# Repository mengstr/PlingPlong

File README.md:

## PingPlong

This is a small (10x20cm 4x8") portable battery-operated synth with a two octave touch keyboard and four voice polyphonic digital sound. A video of the board in action is available at http://youtu.be/FlVGMttL9SU

Two microcontrollers are used on the board - a Microchip PIC18F44K22 for the user interface and a Atmel ATMEGA328 for the sound generation.

The PIC18 is using the internal CMTU module for capacitively sensing the 24 touch keys. It is also in charge of scanning the 15 tactile buttons, refreshing the 15 status LEDs and the 7-segment displays, and polling the Rotary Encoder.

Whenever a padis touched or the rotary encoder is turned a standard Note On/Off or Control Change MIDI message is sent to the ATMEGA328 for playing.

Currently the MEGA328 is running a straight copy of the [Midi Vampire-I](http://wiki.openmusiclabs.com/wiki/MidiVamp1) firmware. The MEGA328 is also connected to a SD-card connector for future use - I want to do firmware updates via the SD card.

The sound-generating part is contained in a 5x5cm "selfcontained" area to the right on the pcb having pads and via holes for power, midi and SD-card signals. This makes it easy to replace just the synth with something else than the MidiVamp. Just design a new 5x5 cm pcb and solder it to the pads on the main board and it's done.

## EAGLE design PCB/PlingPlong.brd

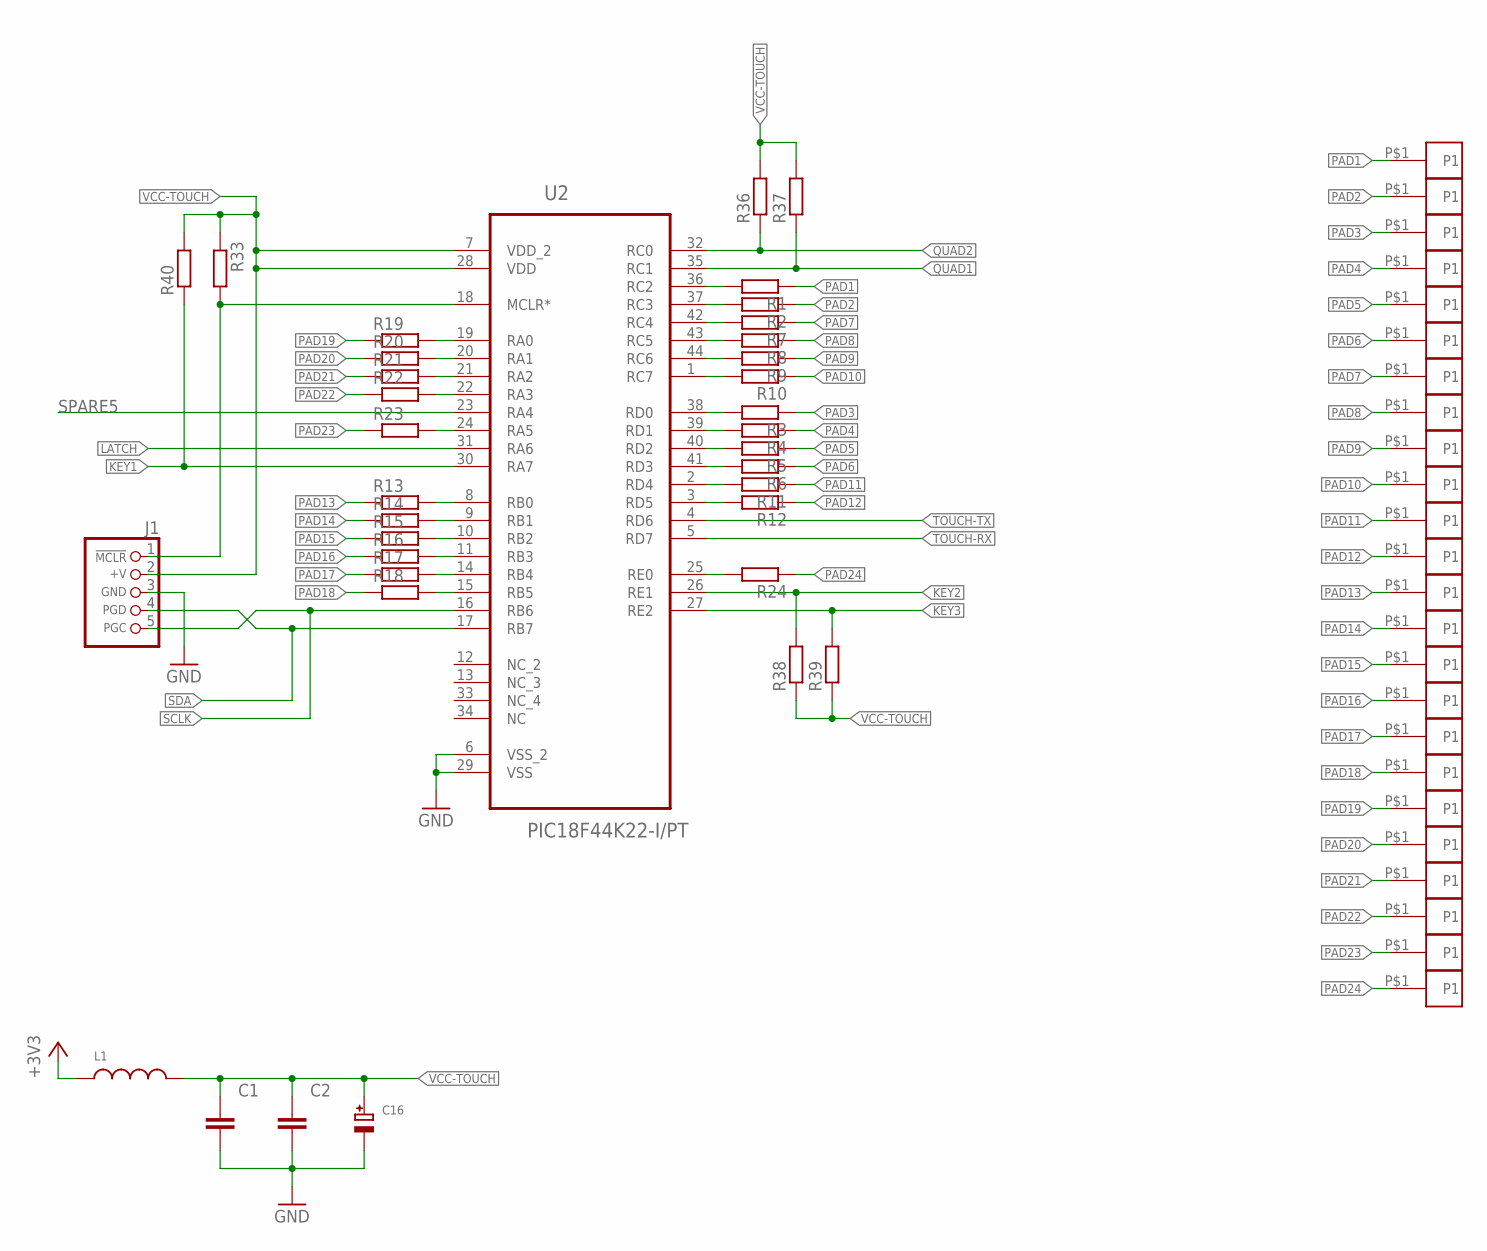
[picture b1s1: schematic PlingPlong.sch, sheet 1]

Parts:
C1, C2: CAPACITOR_NPOL-0805; C805
C16: CAP_TANTALUMD/7343_WAVE; EIA7343-31/D-W
J1: CON_HEADER_PRG_PIC_ICSPB; HEADER_PRG_1X05_ICSP_B
L1: INDUCTOR0805; 0805
P1, P2, P3, P4, P5, P6, P7, P8, P9, P10, P11, P12, P13, P14, P15, P16, P17, P18, P19, P20, P21, P22, P23, P24: PAD-NOSTOP; PAD1X1NOSTOP
R1, R2, R3, R4, R5, R6, R7, R8, R9, R10, R11, R12, R13, R14, R15, R16, R17, R18, R19, R20, R21, R22, R23, R24, R33, R36, R37, R38, R39, R40: R-EU_R0805W; R0805W
U2: PIC18F44K22-I/PT; QFP80P1200X1200X120-44N

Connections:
+3V3: L1.1; also elsewhere on the board
GND: C1.2, C2.2, C16.-, J1.3 (GND), U2.6 (VSS_2), U2.29 (VSS); also elsewhere on the board
KEY1: R40.1, U2.30 (RA7); also elsewhere on the board
KEY2: R38.2, U2.26 (RE1); also elsewhere on the board
KEY3: R39.2, U2.27 (RE2); also elsewhere on the board
LATCH: U2.31 (RA6); also elsewhere on the board
unnamed: R13.2, U2.8 (RB0)
unnamed: R14.2, U2.9 (RB1)
unnamed: R15.2, U2.10 (RB2)
unnamed: R16.2, U2.11 (RB3)
unnamed: R17.2, U2.14 (RB4)
unnamed: R18.2, U2.15 (RB5)
unnamed: R23.2, U2.24 (RA5)
unnamed: R19.2, U2.19 (RA0)
unnamed: R20.2, U2.20 (RA1)
unnamed: R21.2, U2.21 (RA2)
unnamed: R22.2, U2.22 (RA3)
unnamed: R1.2, U2.36 (RC2)
unnamed: R2.2, U2.37 (RC3)
unnamed: R7.2, U2.42 (RC4)
unnamed: R8.2, U2.43 (RC5)
unnamed: R9.2, U2.44 (RC6)
unnamed: R10.2, U2.1 (RC7)
unnamed: R24.2, U2.25 (RE0)
unnamed: J1.1 (/MCLR), R33.2, U2.18 (MCLR*)
unnamed: R12.2, U2.3 (RD5)
unnamed: R11.2, U2.2 (RD4)
unnamed: R6.2, U2.41 (RD3)
unnamed: R5.2, U2.40 (RD2)
unnamed: R4.2, U2.39 (RD1)
unnamed: R3.2, U2.38 (RD0)
PAD1: P1.P$1, R1.1
PAD2: P2.P$1, R2.1
PAD3: P3.P$1, R3.1
PAD4: P4.P$1, R4.1
PAD5: P5.P$1, R5.1
PAD6: P6.P$1, R6.1
PAD7: P7.P$1, R7.1
PAD8: P8.P$1, R8.1
PAD9: P9.P$1, R9.1
PAD10: P10.P$1, R10.1
PAD11: P11.P$1, R11.1
PAD12: P12.P$1, R12.1
PAD13: P13.P$1, R13.1
PAD14: P14.P$1, R14.1
PAD15: P15.P$1, R15.1
PAD16: P16.P$1, R16.1
PAD17: P17.P$1, R17.1
PAD18: P18.P$1, R18.1
PAD19: P19.P$1, R19.1
PAD20: P20.P$1, R20.1
PAD21: P21.P$1, R21.1
PAD22: P22.P$1, R22.1
PAD23: P23.P$1, R23.1
PAD24: P24.P$1, R24.1
QUAD1: R37.1, U2.35 (RC1); also elsewhere on the board
QUAD2: R36.1, U2.32 (RC0); also elsewhere on the board
SCLK: J1.5 (PGC), U2.16 (RB6); also elsewhere on the board
SDA: J1.4 (PGD), U2.17 (RB7); also elsewhere on the board
SPARE5: U2.23 (RA4)
TOUCH-RX: U2.5 (RD7); also elsewhere on the board
TOUCH-TX: U2.4 (RD6); also elsewhere on the board
VCC-TOUCH: C1.1, C2.1, C16.+, J1.2 (+V), L1.2, R33.1, R36.2, R37.2, R38.1, R39.1, R40.2, U2.7 (VDD_2), U2.28 (VDD)

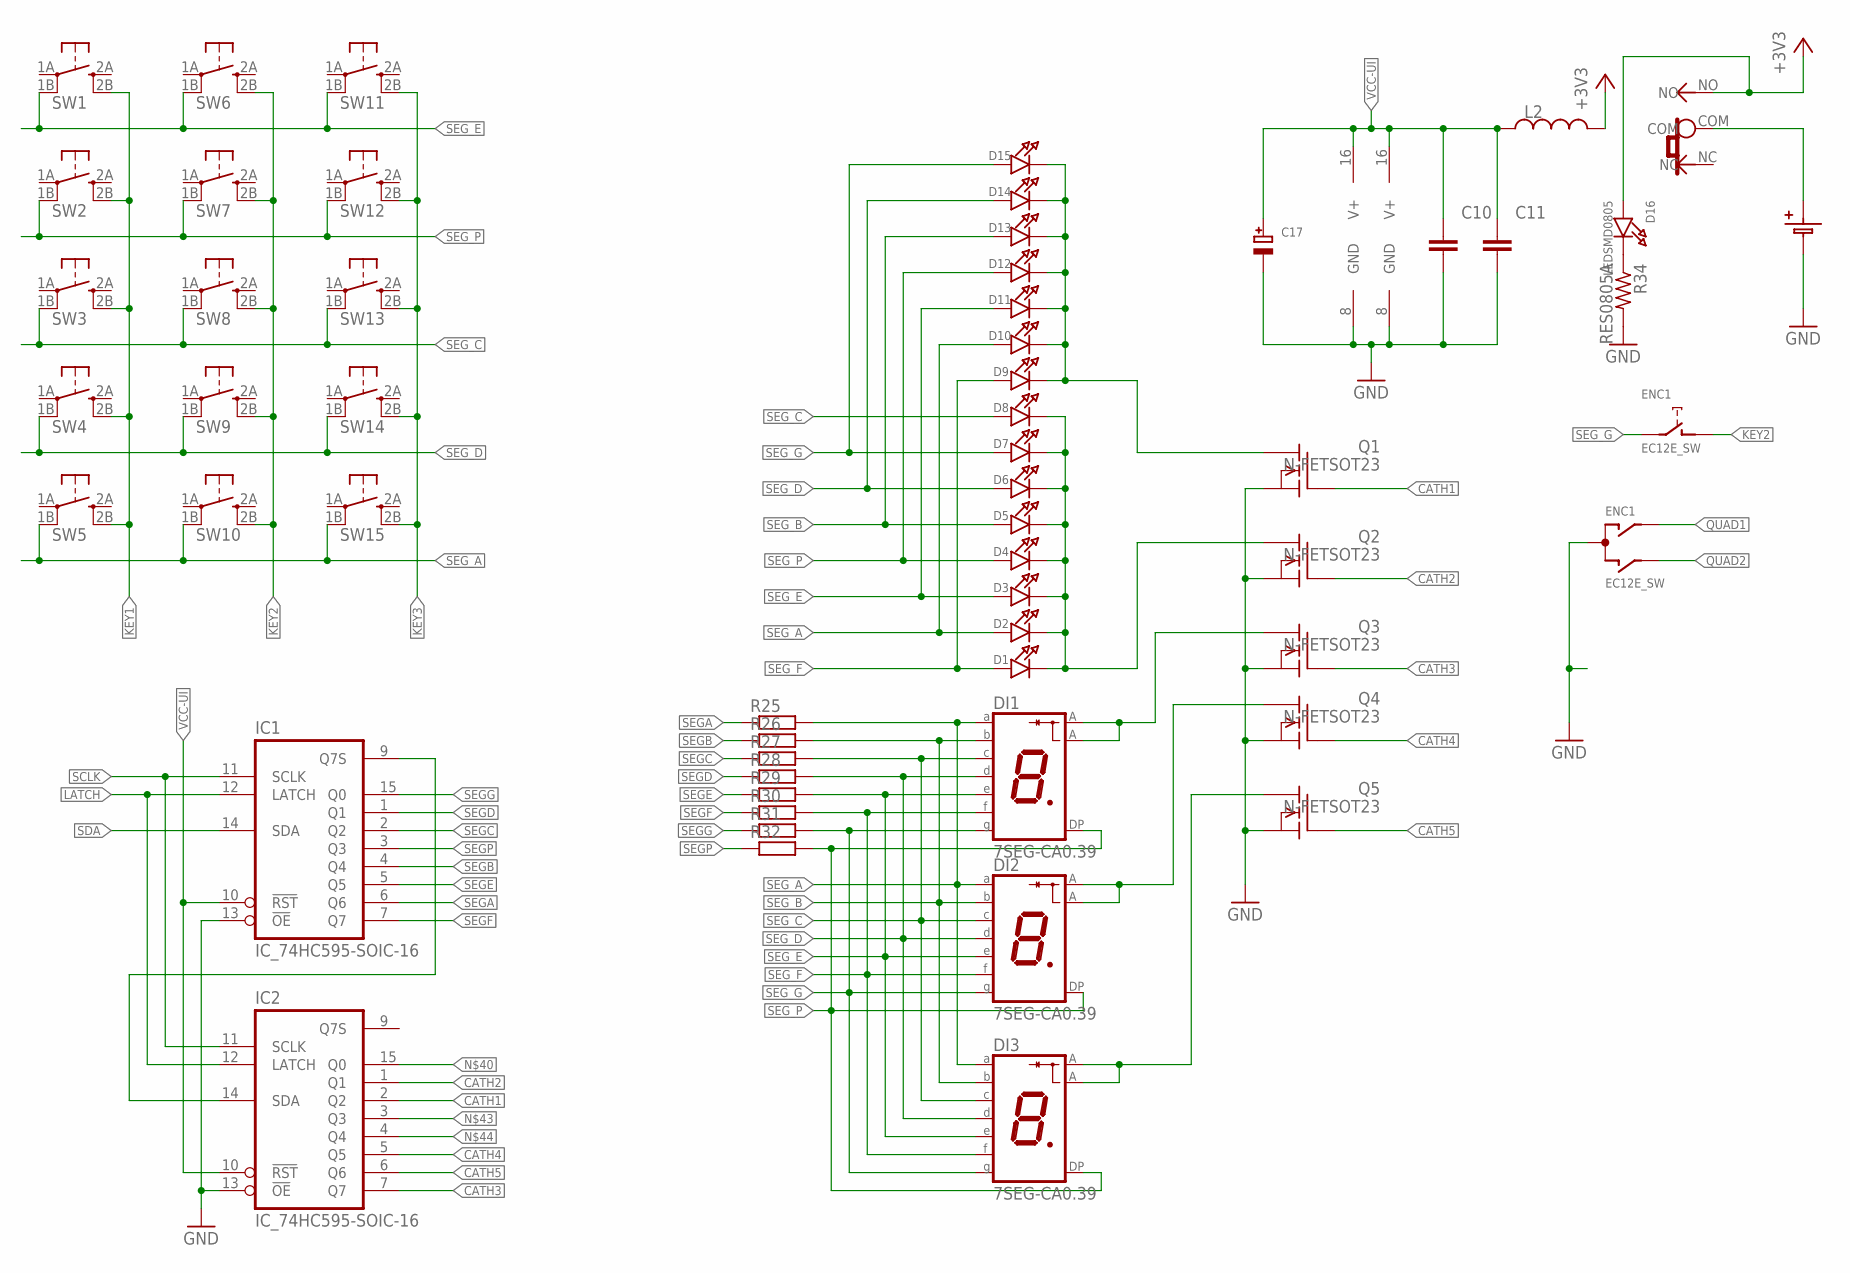
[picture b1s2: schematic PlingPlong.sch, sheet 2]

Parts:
BA1: BATTERY1-123PIN; BATTERY-CR123A-PINS
C10, C11: CAPACITOR_NPOL-0805; C805
C17: CAP_TANTALUMD/7343_WAVE; EIA7343-31/D-W
D1, D2, D3, D4, D5, D6, D7, D8, D9, D10, D11, D12, D13, D14, D15: LED3MM
D16: LEDSMD0805; CHIPLED_0805
DI1, DI2, DI3: 7SEG-CA0.39; LG3911
ENC1: EC12E_SW; ALPS_EC12E_SW
IC1, IC2: IC_74HC595-SOIC-16; SOIC-16
L2: INDUCTOR0805; 0805
Q1, Q2, Q3, Q4, Q5: N-FETSOT23; SOT23
R25, R26, R27, R28, R29, R30, R31, R32: R-EU_R0805W; R0805W
R34: RES0805A; R0805A
SW1, SW2, SW3, SW4, SW5, SW6, SW7, SW8, SW9, SW10, SW11, SW12, SW13, SW14, SW15: TACTILETACT-6X6-PTH; TACTILE-PTH
SW16: SLIDESWITCH-PCM12; PCM12

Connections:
+3V3: D16.A, L2.2, SW16.NO; also elsewhere on the board
CATH1: IC2.2 (Q2), Q1.1 (G)
CATH2: IC2.1 (Q1), Q2.1 (G)
CATH3: IC2.7 (Q7), Q3.1 (G)
CATH4: IC2.5 (Q5), Q4.1 (G)
CATH5: IC2.6 (Q6), Q5.1 (G)
CATH_1: D9.C, D10.C, D11.C, D12.C, D13.C, D14.C, D15.C, Q1.3 (D)
CATH_2: D1.C, D2.C, D3.C, D4.C, D5.C, D6.C, D7.C, D8.C, Q2.3 (D)
CATH_3: DI1.P$3 (A), DI1.P$8 (A), Q3.3 (D)
CATH_4: DI2.P$3 (A), DI2.P$8 (A), Q4.3 (D)
CATH_5: DI3.P$3 (A), DI3.P$8 (A), Q5.3 (D)
GND: BA1.NEG, C10.2, C11.2, C17.-, ENC1.C, IC1.8 (GND), IC1.13 (!OE), IC2.8 (GND), IC2.13 (!OE), Q1.2 (S), Q2.2 (S), Q3.2 (S), Q4.2 (S), Q5.2 (S), R34.2; also elsewhere on the board
KEY1: SW1.2B, SW2.2B, SW3.2B, SW4.2B, SW5.2B; also elsewhere on the board
KEY2: ENC1.D (1), SW6.2B, SW7.2B, SW8.2B, SW9.2B, SW10.2B; also elsewhere on the board
KEY3: SW11.2B, SW12.2B, SW13.2B, SW14.2B, SW15.2B; also elsewhere on the board
LATCH: IC1.12 (LATCH), IC2.12 (LATCH); also elsewhere on the board
unnamed: IC1.9 (Q7S), IC2.14 (SDA)
unnamed: BA1.POS (POS1), SW16.COM
unnamed: D16.C, R34.1
QUAD1: ENC1.A; also elsewhere on the board
QUAD2: ENC1.B; also elsewhere on the board
SCLK: IC1.11 (SCLK), IC2.11 (SCLK); also elsewhere on the board
SDA: IC1.14 (SDA); also elsewhere on the board
SEGA: IC1.6 (Q6), R25.1
SEGB: IC1.4 (Q4), R26.1
SEGC: IC1.2 (Q2), R27.1
SEGD: IC1.1 (Q1), R28.1
SEGE: IC1.5 (Q5), R29.1
SEGF: IC1.7 (Q7), R30.1
SEGG: IC1.15 (Q0), R31.1
SEGP: IC1.3 (Q3), R32.1
SEG_A: D2.A, D10.A, DI1.P$10 (A), DI2.P$10 (A), DI3.P$10 (A), R25.2, SW5.1B, SW10.1B, SW15.1B
SEG_B: D5.A, D13.A, DI1.P$9 (B), DI2.P$9 (B), DI3.P$9 (B), R26.2
SEG_C: D8.A, DI1.P$7 (C), DI2.P$7 (C), DI3.P$7 (C), R27.2, SW3.1B, SW8.1B, SW13.1B
SEG_D: D6.A, D14.A, DI1.P$5 (D), DI2.P$5 (D), DI3.P$5 (D), R28.2, SW4.1B, SW9.1B, SW14.1B
SEG_E: D3.A, D11.A, DI1.P$2 (E), DI2.P$2 (E), DI3.P$2 (E), R29.2, SW1.1B, SW6.1B, SW11.1B
SEG_F: D1.A, D9.A, DI1.P$1 (F), DI2.P$1 (F), DI3.P$1 (F), R30.2
SEG_G: D7.A, D15.A, DI1.P$6 (G), DI2.P$6 (G), DI3.P$6 (G), ENC1.E (2), R31.2
SEG_P: D4.A, D12.A, DI1.P$4 (DP), DI2.P$4 (DP), DI3.P$4 (DP), R32.2, SW2.1B, SW7.1B, SW12.1B
VCC-UI: C10.1, C11.1, C17.+, IC1.10 (!RST), IC1.16 (V+), IC2.10 (!RST), IC2.16 (V+), L2.1

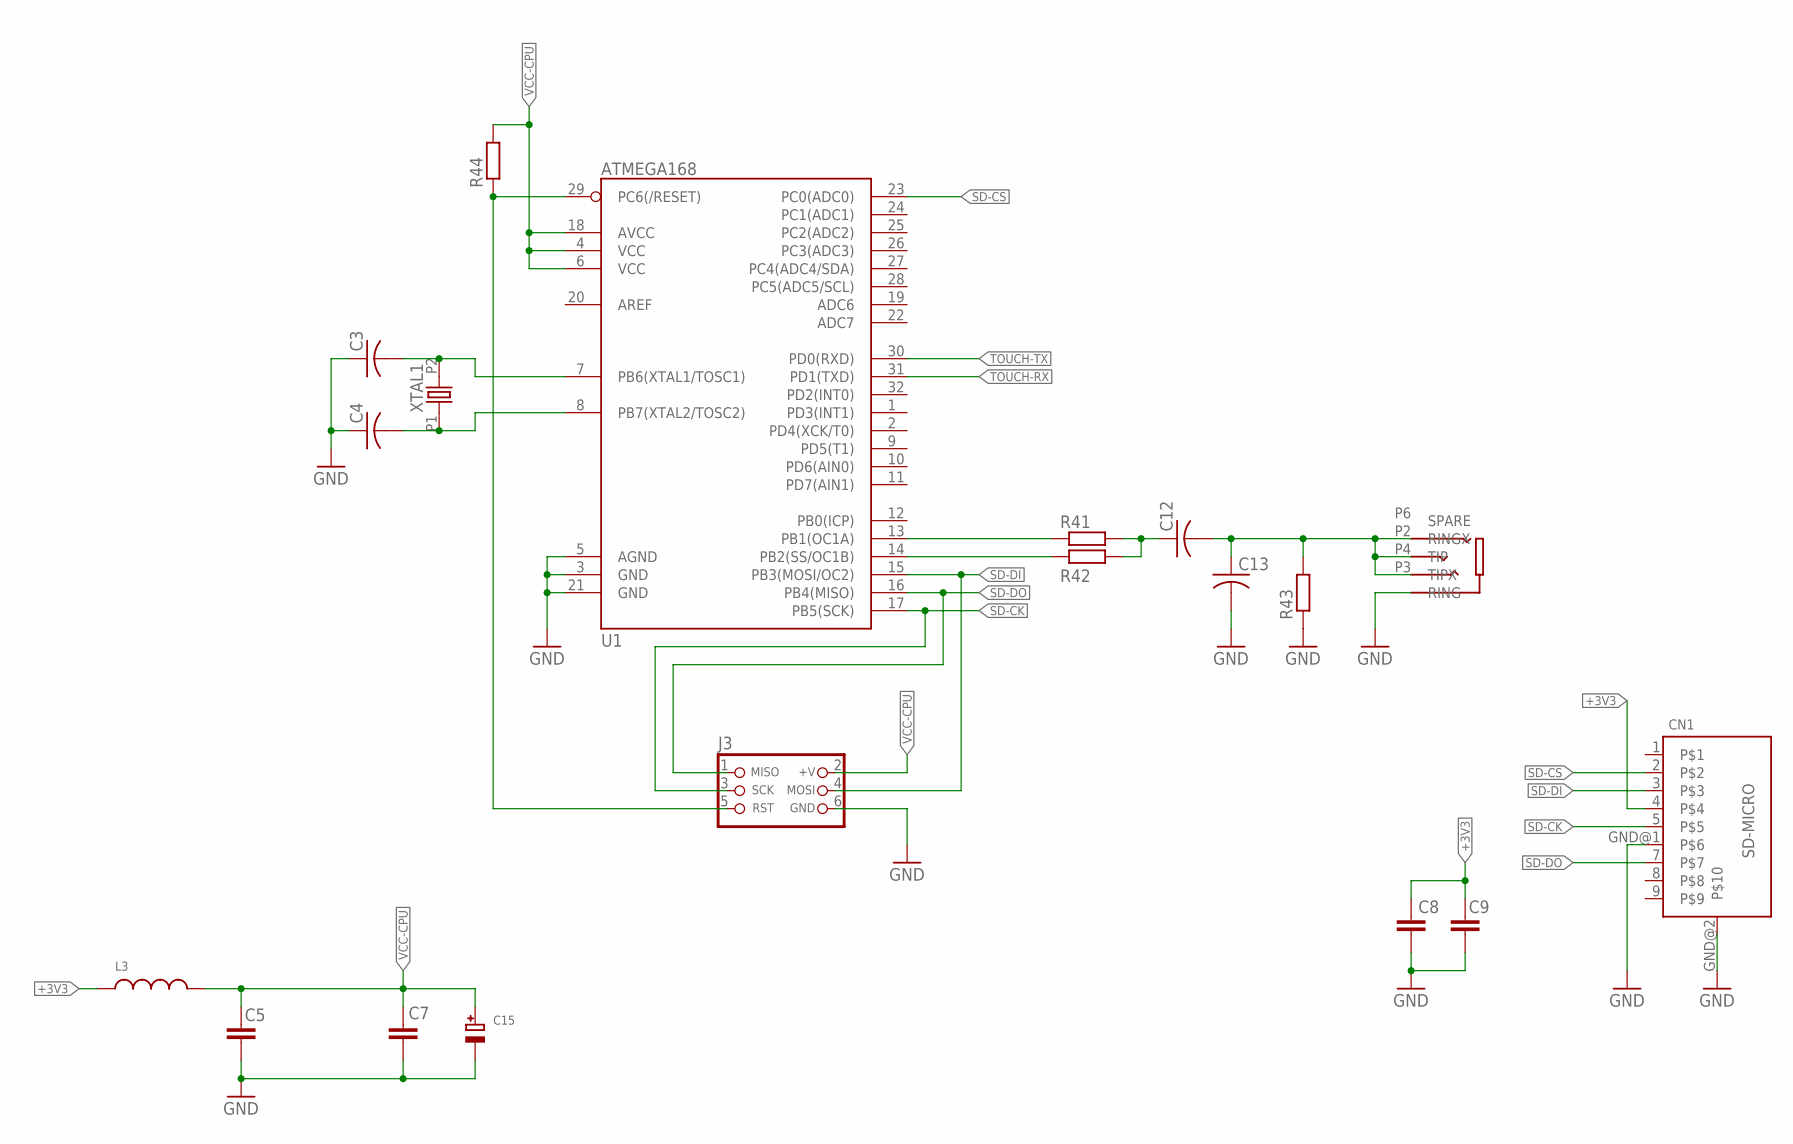
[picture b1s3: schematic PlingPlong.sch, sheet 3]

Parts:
C3, C4, C13: C-USC0805; C0805
C5, C7, C8, C9: CAPACITOR_NPOL-0805; C805
C12: C-USC1206; C1206
C15: CAP_TANTALUMD/7343_WAVE; EIA7343-31/D-W
CN1: SD-MICRO; MICROSD-TFP09
J3: CON_HEADER_PRG_AVR_ICSP; HEADER_PRG_2X03
L3: INDUCTOR0805; 0805
R41, R42, R43, R44: R-EU_R0805W; R0805W
U1: ATMEGA168; TQFP32-08
U$2: JACK4-PJ320; PJ-320E
XTAL1: OSC-XTAL-HC-49U-PTH; HC-49U-PTH

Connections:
+3V3: C8.1, C9.1, CN1.4, L3.1; also elsewhere on the board
CPU-RESET: J3.5 (RST), R44.1, U1.29 (PC6(/RESET))
GND: C3.1, C4.1, C5.2, C7.2, C8.2, C9.2, C13.2, C15.-, CN1.GND@1, CN1.GND@2, J3.6 (GND), R43.1, U1.3 (GND), U1.5 (AGND), U1.21 (GND), U$2.P5 (RING); also elsewhere on the board
unnamed: R41.1, U1.13 (PB1(OC1A))
unnamed: R42.1, U1.14 (PB2(SS/OC1B))
unnamed: C12.1, R41.2, R42.2
unnamed: C12.2, C13.1, R43.2, U$2.P2 (RINGX), U$2.P3 (TIPX), U$2.P4 (TIP)
unnamed: C3.2, U1.7 (PB6(XTAL1/TOSC1)), XTAL1.P2 (2)
unnamed: C4.2, U1.8 (PB7(XTAL2/TOSC2)), XTAL1.P1 (1)
SD-CK: CN1.5, J3.3 (SCK), U1.17 (PB5(SCK))
SD-CS: CN1.2, U1.23 (PC0(ADC0))
SD-DI: CN1.3, J3.4 (MOSI), U1.15 (PB3(MOSI/OC2))
SD-DO: CN1.7, J3.1 (MISO), U1.16 (PB4(MISO))
TOUCH-RX: U1.31 (PD1(TXD)); also elsewhere on the board
TOUCH-TX: U1.30 (PD0(RXD)); also elsewhere on the board
VCC-CPU: C5.1, C7.1, C15.+, J3.2 (+V), L3.2, R44.2, U1.4 (VCC), U1.6 (VCC), U1.18 (AVCC)

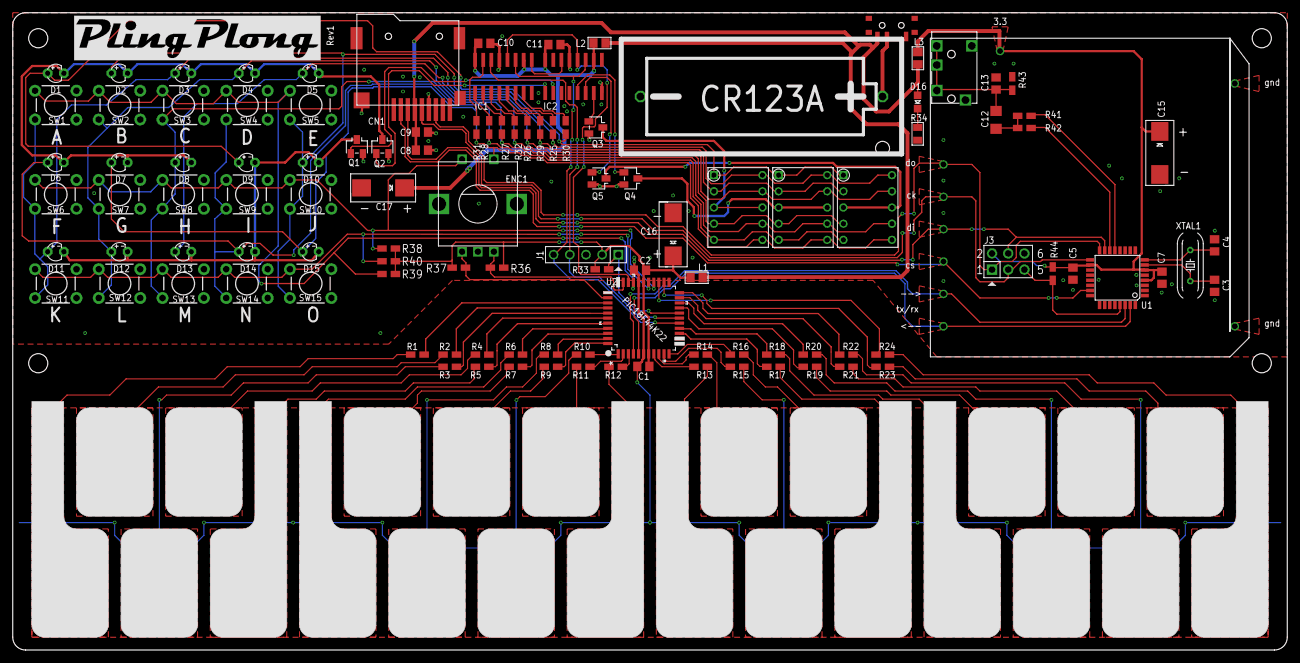
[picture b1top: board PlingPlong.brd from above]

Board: 2 copper layers, 200.0 x 100.0 mm, 136 parts (0 on the bottom side), 104 nets.

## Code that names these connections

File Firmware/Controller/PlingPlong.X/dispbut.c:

#include <stdint.h>         /* For uint8_t definition */
#include <stdbool.h>        /* For true/false definition */
#include <xc.h>
#include "dispbut.h"

#define KEY1            PORTAbits.RA7
#define KEY2            PORTEbits.RE1
#define KEY3            PORTEbits.RE2

#define LATCH595        LATAbits.LA6
#define CLK595          LATBbits.LB6
#define DATA595         LATBbits.LB7


volatile uint8_t    disp[3];
volatile uint16_t   leds;
volatile uint16_t   keys;
volatile uint8_t    butt;

const uint8_t charmap[]={
    0x00,0x82,0x21,0x00,0x00,0x00,0x00,0x02,0x39,0x0f,0x00,0x00,0x00,0x40,0x80,0x52,	//  !"#$%&'()*+,-./
    0x3f,0x06,0x5b,0x4f,0x66,0x6d,0x7d,0x07,0x7f,0x6f,0x09,0x00,0x00,0x48,0x00,0x53,	// 0123456789:;<=>?
    0x00,0x77,0x7c,0x39,0x5e,0x79,0x71,0x6f,0x76,0x06,0x1e,0x70,0x38,0x37,0x54,0x3f,	// @ABCDEFGHIJKLMNO
    0x73,0x67,0x50,0x6d,0x78,0x3e,0x00,0x00,0x00,0x6e,0x00,0x39,0x00,0x0f,0x00,0x08,	// PQRSTUVWXYZ[\]^
    0x63,0x5f,0x7c,0x58,0x5e,0x7b,0x71,0x6f,0x74,0x02,0x1e,0x00,0x06,0x00,0x54,0x5c,	// `abcdefghijklmno
    0x73,0x67,0x50,0x6d,0x78,0x1c,0x00,0x00,0x00,0x6e,0x00,0x39,0x30,0x0f,0x00,0x00, 	// pqrstuvwxyz{|}~
    };



void ShiftBit(bool v) {
    if (v) DATA595=1; else DATA595=0;
    NOP();
    CLK595=1;
    NOP();
    CLK595=0;
}

void ShiftByte(uint8_t v) {
    ShiftBit(v&0x80);
    ShiftBit(v&0x40);
    ShiftBit(v&0x20);
    ShiftBit(v&0x10);
    ShiftBit(v&0x08);
    ShiftBit(v&0x04);
    ShiftBit(v&0x02);
    ShiftBit(v&0x01);
}



void RefreshDisp(void) {
    static uint8_t cath=0;
    uint8_t v;
    uint8_t no;

    cath++;
    if (cath==6) {
        cath=0;
    }

    if (cath==0) {
        keys=0;
        butt=0;

        LATCH595=0;
        ShiftByte(0x00);
        ShiftByte(~0x20);
        LATCH595=1;
        NOP();
        NOP();
        NOP();
        NOP();
        NOP();
        if (KEY1==0) keys|=0x0001;
        if (KEY2==0) keys|=0x0020;
        if (KEY3==0) keys|=0x0400;

        LATCH595=0;
        ShiftByte(0x00);
        ShiftByte(~0x08);
        LATCH595=1;
        NOP();
        NOP();
        NOP();
        NOP();
        NOP();
        if (KEY1==0) keys|=0x0002;
        if (KEY2==0) keys|=0x0040;
        if (KEY3==0) keys|=0x0800;

        LATCH595=0;
        ShiftByte(0x00);
        ShiftByte(~0x04);
        LATCH595=1;
        NOP();
        NOP();
        NOP();
        NOP();
        NOP();
        if (KEY1==0) keys|=0x0004;
        if (KEY2==0) keys|=0x0080;
        if (KEY3==0) keys|=0x1000;

        LATCH595=0;
        ShiftByte(0x00);
        ShiftByte(~0x02);
        LATCH595=1;
        NOP();
        NOP();
        NOP();
        NOP();
        NOP();
        if (KEY1==0) keys|=0x0008;
        if (KEY2==0) keys|=0x0100;
        if (KEY3==0) keys|=0x2000;

        LATCH595=0;
        ShiftByte(0x00);
        ShiftByte(~0x40);
        LATCH595=1;
        NOP();
        NOP();
        NOP();
        NOP();
        NOP();
        if (KEY1==0) keys|=0x0010;
        if (KEY2==0) keys|=0x0200;
        if (KEY3==0) keys|=0x4000;

        LATCH595=0;
        ShiftByte(0x00);
        ShiftByte(~0x01);
        LATCH595=1;
        NOP();
        NOP();
        NOP();
        NOP();
        NOP();
        if (KEY2==0) butt=1;

        return;
    }

    v=0;
    if (cath==1) {
        if (leds&0x0100) v|=0x80;
        if (leds&0x0200) v|=0x40;
        if (leds&0x0400) v|=0x20;
        if (leds&0x0800) v|=0x08;
        if (leds&0x1000) v|=0x10;
        if (leds&0x2000) v|=0x02;
        if (leds&0x4000) v|=0x01;
    }
    if (cath==2) {
        if (leds&0x0001) v|=0x80;
        if (leds&0x0002) v|=0x40;
        if (leds&0x0004) v|=0x20;
        if (leds&0x0008) v|=0x08;
        if (leds&0x0010) v|=0x10;
        if (leds&0x0020) v|=0x02;
        if (leds&0x0040) v|=0x01;
        if (leds&0x0080) v|=0x04;
    }
    if (cath==3 || cath==4 || cath==5) {
        no=cath-3;
        if (disp[no]&0x01) v|=0x40;     // SEG_A ~
        if (disp[no]&0x02) v|=0x10;     // SEG_B ~
        if (disp[no]&0x04) v|=0x04;     // SEG_C ~
        if (disp[no]&0x08) v|=0x02;     // SEG_D ~
        if (disp[no]&0x10) v|=0x08;     // SEG_E
        if (disp[no]&0x20) v|=0x20;     // SEG_F
        if (disp[no]&0x40) v|=0x80;     // SEG_G
        if (disp[no]&0x80) v|=0x01;     // SEG_H
    }

    LATCH595=0;
    ShiftBit(cath==3);
    ShiftBit(cath==5);
    ShiftBit(cath==4);
    ShiftBit(false);
    ShiftBit(false);
    ShiftBit(cath==1);
    ShiftBit(cath==2);
    ShiftBit(false);
    ShiftByte(v);
    LATCH595=1;
}


void DispValue(uint16_t value) {
    uint16_t t;
    uint8_t dp0,dp1,dp2;
    t=value;

    dp0=0;
    dp1=0;
    dp2=0;
    if (t>3999) {
        t=0;
        dp0=0x80;
        dp1=0x80;
        dp2=0x80;
    } else if (t>2999) {
        dp0=0x80;
        t=t-3000;
    } else if (t>1999) {
        dp1=0x80;
        t=t-2000;
    } else if (t>999) {
        dp2=0x80;
        t=t-1000;
    }
    disp[2]=charmap[16+(t%10)] | dp2;
    t=t/10;
    disp[1]=charmap[16+(t%10)] | dp1;
    t=t/10;
    disp[0]=charmap[16+(t%10)] | dp0;
}

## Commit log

2013-10-30 Rev 1
2013-10-30 Photo of soldered pcb
2013-10-30 Small photo of soldered pcb
2013-12-18 Added Easter Eggs for HAD competition
2013-12-18 Added block diagram

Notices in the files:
parts and their libraries:
SparkFun: Licensing: CC v3.0 Share-Alike You are welcome to use this library for commercial purposes.
microbuilder: This work is placed in the public domain, and may be freely used for commercial and non-commercial work with the following conditions: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
